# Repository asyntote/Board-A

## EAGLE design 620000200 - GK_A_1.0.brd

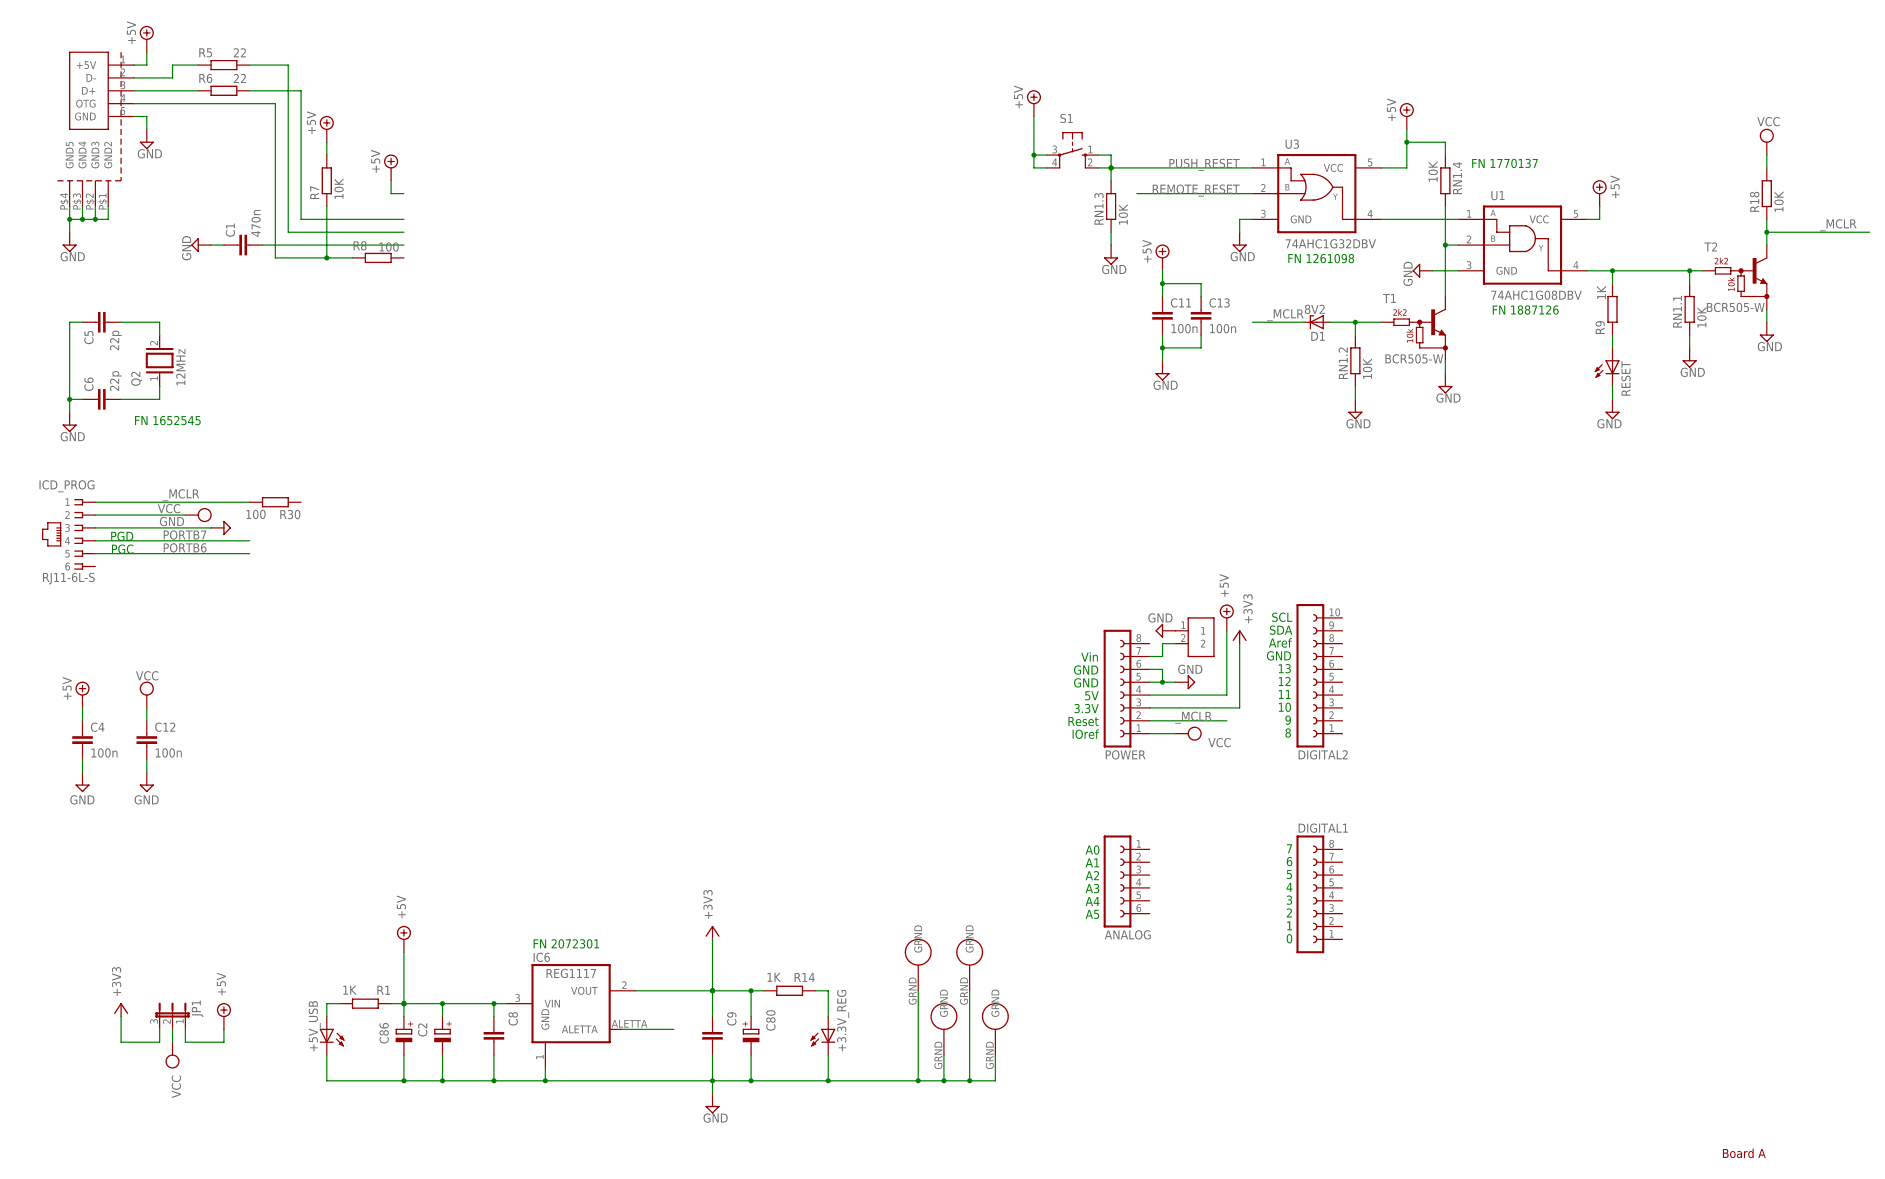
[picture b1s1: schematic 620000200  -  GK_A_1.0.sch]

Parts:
+3.3V_REG, +5V_USB: LEDCHIPLED_0805; CHIPLED_0805
ANALOG: FE06-1; FE06
C1: 470n; C0805
C2, C80, C86: 47u; 153CLV-0605
C4, C11, C12, C13: 100n; C0805
C5, C6: 22p; C0805
C8, C9: 100n; C0805K
D1: 8V2; SOT23
DIGITAL1: FE08-1; FE08
DIGITAL2: FE10-1; FE10
IC6: REG1117
ICD_PROG: RJ11-6L-S; RJ11-NO_SHIELD
JP1: JP2E; JP2
POWER: FE08-1; FE08
Q2: 12MHz; QS
R1, R14: 1K; R0805W
R5, R6: 22; R0805W
R7, R18: 10K; R0805
R8: 100; R0805
R9: 1K; R0805
R30: 100; R0805W
RESET: LEDCHIPLED_0805; CHIPLED_0805
RN1: 10K; CTS-744*083
S1: 10-XX; B3F-10XX
T1, T2: BCR505-W; SOT23-W_INFINEON
U1: 74AHC1G08DBV; SOT23-5
U3: 74AHC1G32DBV; SOT23-5
U$1, U$2, U$3, U$4: GKHOLE
U$7: USB_SMD; USB_MINI_SMD
U$8: GKHEAD2; HEAD2

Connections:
+3V3: C9.2, C80.+, IC6.2 (VOUT), JP1.3, POWER.3, R14.1
+5V: C2.+, C4.1, C8.2, C11.1, C13.1, C86.+, IC6.3 (VIN), JP1.1, POWER.4, R1.2, R7.2, RN1.4 (1), S1.3, S1.4 (P1), U1.5 (VCC), U3.5 (VCC), U$7.1 (+5V)
ALETTA: IC6.ALETTA
GND: +3.3V_REG.C, +5V_USB.C, C1.1, C2.-, C4.2, C5.1, C6.1, C8.1, C9.1, C11.2, C12.2, C13.2, C80.-, C86.-, IC6.1 (GND), ICD_PROG.3, POWER.5, POWER.6, RESET.C, RN1.1, RN1.2 (1), RN1.3 (1), T1.2 (E), T2.2 (E), U1.3 (GND), U3.3 (GND), U$1.GRND, U$2.GRND, U$3.GRND, U$4.GRND, U$7.5 (GND), U$7.P$1 (GND2), U$7.P$2 (GND3), U$7.P$3 (GND4), U$7.P$4 (GND5), U$8.1
unnamed: +5V_USB.A, R1.1
unnamed: R9.2, RESET.A
unnamed: +3.3V_REG.A, R14.2
unnamed: U1.1 (A), U3.4 (Y)
unnamed: C5.2, Q2.2
unnamed: POWER.7, U$8.2
unnamed: R7.1, R8.1, U$7.4 (OTG)
unnamed: C6.2, Q2.1
unnamed: RN1.5 (2), T1.3 (C), U1.2 (B)
unnamed: R9.1, RN1.8 (2), T2.1 (B), U1.4 (Y)
unnamed: R5.2, U$7.2 (D-)
unnamed: D1.1 (A), RN1.7 (2), T1.1 (B)
unnamed: R6.2, U$7.3 (D+)
PORTB6: ICD_PROG.5
PORTB7: ICD_PROG.4
PUSH_RESET: RN1.6 (2), S1.1 (S), S1.2 (S1), U3.1 (A)
REMOTE_RESET: U3.2 (B)
VCC: C12.1, ICD_PROG.2, JP1.2, POWER.1, R18.2
_MCLR: D1.3 (C), ICD_PROG.1, POWER.2, R18.1, R30.1, T2.3 (C)

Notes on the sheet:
Board A
SDA
SCL
GND
Aref
Vin
3.3V
Reset
IOref
PGD
PGC
FN 1770137
FN 1887126
FN 1261098
FN 2072301
FN 1652545

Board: 2 copper layers, 45 parts (21 on the bottom side), 19 nets, no tracks yet.

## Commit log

2017-10-17 Start with files
2018-05-08 Add Pic18F67K40 TQFP64
2019-11-06 Progetto pronto per rifare con le nuove MCU. Mantenuto : Alimentazione Reset Struttura arduino compatibile

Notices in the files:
parts and their libraries:
74ah: Copyright (C) 2007, Bob Starr
m-pad-2.1: License : GNU General Public License version 2 (see bottom)
